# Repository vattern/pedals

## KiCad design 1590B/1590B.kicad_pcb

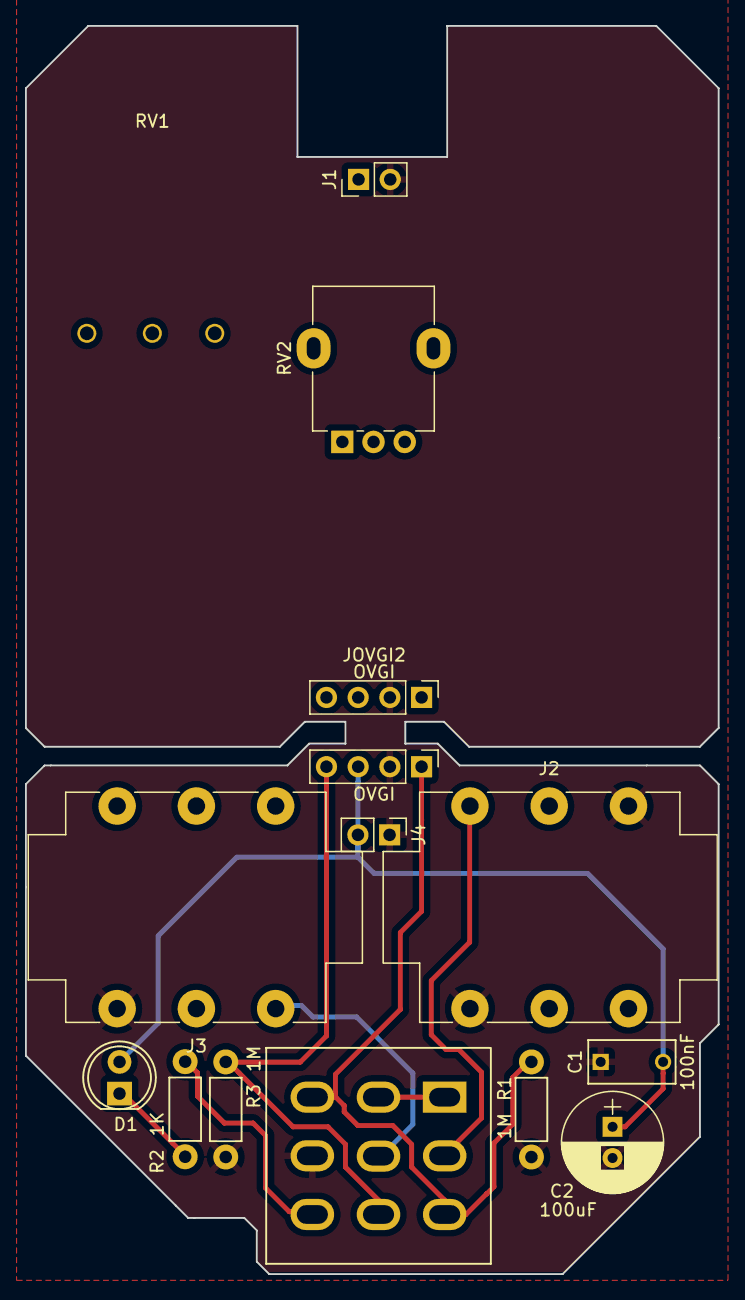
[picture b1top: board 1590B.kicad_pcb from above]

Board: 2 copper layers, 55.5 x 100.0 mm, 16 parts (0 on the bottom side), 9 nets.

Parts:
C1: 100nF; C_Rect_L7_W3.5_P5
C2: 100uF; CP_Radial_D8.0mm_P2.50mm
D1: LED; LED-5MM
J1, J4: V+ GND; PinHeader_1x02_P2.54mm_Vertical
J2, J3: NMJ6HCD2; Jack_6.35mm_Neutrik_NMJ6HCD2_Horizontal
JOVGI1, JOVGI2: OVGI; Pin_Header_Straight_1x04_Pitch2.54mm
N1: Housing; 1590B
R1, R3: 1M; Resistor_Horizontal_RM7mm
R2: 1K; Resistor_Horizontal_RM7mm
RV1: ALPHA-16mm; Potentiometer_ALPHA_RV16106N
RV2: ALPHA-9MM; Potentiometer_Alpha_RD901F-40-00D_Single_Vertical
SW1: SW_3PDT; 3PDT-Footswitch

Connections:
+9V: C1.2, C2.1, D1.2 (A), J1.1, J4.2, JOVGI1.3, JOVGI2.3
GND: C1.1, C2.2, J1.2, J2.S, J2.TN, J3.S, J4.1, JOVGI1.2, JOVGI2.2, R1.2, R3.2, SW1.6 (B)
I: JOVGI1.1, JOVGI2.1, R1.1, SW1.3 (A), SW1.7 (C)
unnamed: D1.1 (K), R2.1
unnamed: SW1.1 (A), SW1.2 (A)
unnamed: J2.T, SW1.4 (B)
unnamed: J3.T, SW1.5 (B)
unnamed: R2.2, SW1.9 (C)
O: JOVGI1.4, JOVGI2.4, R3.1, SW1.8 (C)

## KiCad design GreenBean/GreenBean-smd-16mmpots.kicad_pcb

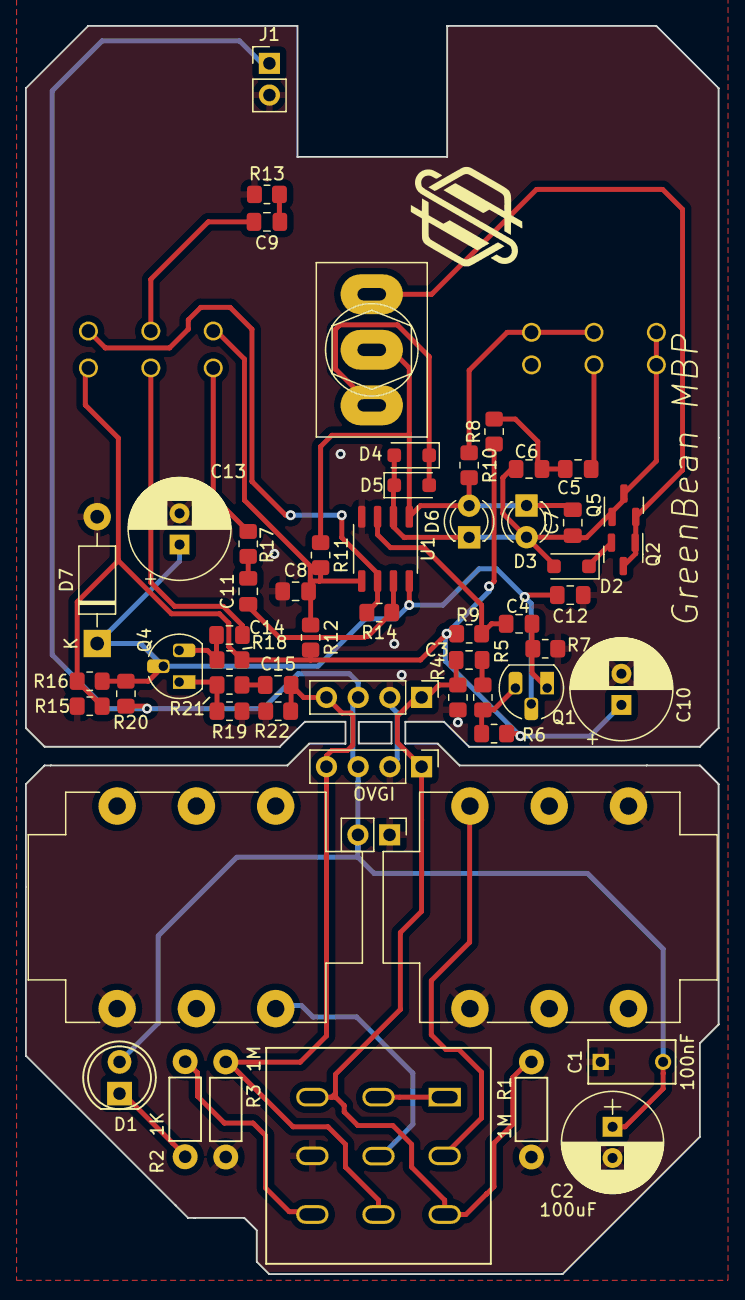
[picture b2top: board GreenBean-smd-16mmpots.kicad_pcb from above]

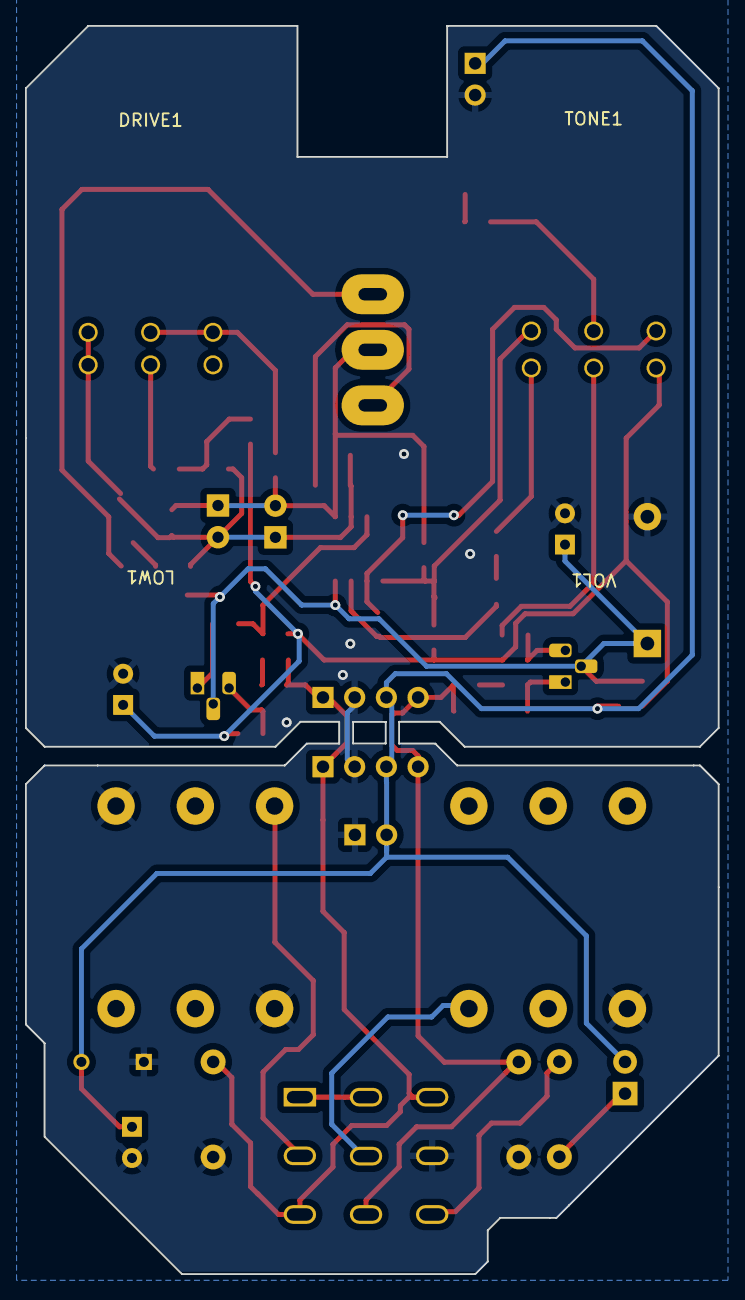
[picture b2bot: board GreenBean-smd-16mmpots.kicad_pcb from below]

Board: 2 copper layers, 55.5 x 100.0 mm, 62 parts (4 on the bottom side), 34 nets.

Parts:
C1: 100nF; C_Rect_L7_W3.5_P5
C2, C13: 100uF; CP_Radial_D8.0mm_P2.50mm
C3: 20n; C_0805_2012Metric_Pad1.18x1.45mm_HandSolder
C4, C11, C15: 1u; C_0805_2012Metric_Pad1.18x1.45mm_HandSolder
C5: 150n; C_0805_2012Metric_Pad1.18x1.45mm_HandSolder
C6: 47n; C_0805_2012Metric_Pad1.18x1.45mm_HandSolder
C7: 51p; C_0805_2012Metric_Pad1.18x1.45mm_HandSolder
C8, C9, C12: 220n; C_0805_2012Metric_Pad1.18x1.45mm_HandSolder
C10: 10uF; CP_Radial_D8.0mm_P2.50mm
C14: 100n; C_0805_2012Metric_Pad1.18x1.45mm_HandSolder
D1: LED; LED-5MM
D2: BAT41; D_SOD-123F
D3, D6: LED; LED_D3.0mm
D4, D5: 1N914; D_SOD-123F
D7: 1N4001; D_DO-41_SOD81_P10.16mm_Horizontal
DRIVE1: 500KA; Potentiometer_ALPHA_RV16106N
J1, J4: V+ GND; PinHeader_1x02_P2.54mm_Vertical
J2, J3: NMJ6HCD2; Jack_6.35mm_Neutrik_NMJ6HCD2_Horizontal
JOVGI1, JOVGI2: OVGI; Pin_Header_Straight_1x04_Pitch2.54mm
LOW1: 20KB; Potentiometer_ALPHA_RV16106N
N1: Housing; 1590B
Q1, Q4: 2SC1815; TO-92L_HandSolder
Q2, Q5: 2N7002; SOT-23
R1, R3: 1M; Resistor_Horizontal_RM7mm
R2: 1K; Resistor_Horizontal_RM7mm
R4: 1M; R_0805_2012Metric_Pad1.20x1.40mm_HandSolder
R5, R11, R14, R17: 1k; R_0805_2012Metric_Pad1.20x1.40mm_HandSolder
R6, R18: 510k; R_0805_2012Metric_Pad1.20x1.40mm_HandSolder
R7, R9, R12, R15, R16, R19, R22: 10k; R_0805_2012Metric_Pad1.20x1.40mm_HandSolder
R8: 4k7; R_0805_2012Metric_Pad1.20x1.40mm_HandSolder
R10: 51k; R_0805_2012Metric_Pad1.20x1.40mm_HandSolder
R13: 220R; R_0805_2012Metric_Pad1.20x1.40mm_HandSolder
R20: 47R; R_0805_2012Metric_Pad1.20x1.40mm_HandSolder
R21: 100R; R_0805_2012Metric_Pad1.20x1.40mm_HandSolder
SW1: SW_3PDT; 3PDT-Footswitch
SW2: SW_SPDT; SW_Toggle_Blue_wSlots
TONE1: 20KB; Potentiometer_ALPHA_RV16106N
U1: RC4558; SO-8_3.9x4.9mm_P1.27mm
VOL1: 100KB; Potentiometer_ALPHA_RV16106N

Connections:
+9V: C1.2, C2.1, D1.2 (A), J1.1, J4.2, JOVGI1.3, JOVGI2.3, R20.2
A: C6.2, C7.1, D2.2 (A), D3.2 (A), D4.2 (A), D5.1 (K), D6.1 (K), DRIVE1.1, LOW1.3, Q5.1 (G), Q5.3 (D), U1.2 (-)
B: C7.2, D3.1 (K), D6.2 (A), R10.2, R11.1, SW2.2, U1.1
GND: C1.1, C2.2, C8.1, C10.2, C12.1, C13.2, D7.2 (A), J1.2, J2.S, J2.TN, J3.S, J4.1, JOVGI1.2, JOVGI2.2, R1.2, R3.2, R4.1, R7.1, R13.1, R15.1, R19.1, R22.1, SW1.6 (B), U1.4 (V-)
I: C3.1, JOVGI1.1, JOVGI2.1, R1.1, R4.2, SW1.3 (A), SW1.7 (C)
unnamed: C3.2, R5.2
unnamed: C5.1, C6.1, R8.2
unnamed: C5.2, LOW1.2
unnamed: C9.1, R13.2
unnamed: C9.2, TONE1.2
unnamed: C11.1, R14.2, U1.7
unnamed: C11.2, R17.1
unnamed: C14.1, VOL1.2
unnamed: C15.1, R21.2
unnamed: D1.1 (K), R2.1
unnamed: D2.1 (K), Q2.2 (S)
unnamed: D4.1 (K), D5.2 (A), SW2.1
unnamed: DRIVE1.2, DRIVE1.3, R10.1
unnamed: Q1.3 (B), R5.1, R6.1
unnamed: C4.1, Q1.1 (E), R7.2
unnamed: Q2.1 (G), Q2.3 (D), Q5.2 (S), SW2.3
unnamed: C14.2, Q4.3 (B), R18.1
unnamed: Q4.1 (E), R19.2, R21.1
unnamed: R17.2, VOL1.3
unnamed: SW1.1 (A), SW1.2 (A)
unnamed: J2.T, SW1.4 (B)
unnamed: J3.T, SW1.5 (B)
unnamed: R2.2, SW1.9 (C)
unnamed: C4.2, R9.1, U1.3 (+)
unnamed: C8.2, R11.2, R12.1, TONE1.1, U1.5 (+)
unnamed: R14.1, TONE1.3, U1.6 (-)
O: C15.2, JOVGI1.4, JOVGI2.4, R3.1, R22.2, SW1.8 (C)
VB: C10.1, R6.2, R8.1, R9.2, R12.2, R15.2, R16.1, R18.2, VOL1.1
VC: C12.2, C13.1, D7.1 (K), Q1.2 (C), Q4.2 (C), R16.2, R20.1, U1.8 (V+)

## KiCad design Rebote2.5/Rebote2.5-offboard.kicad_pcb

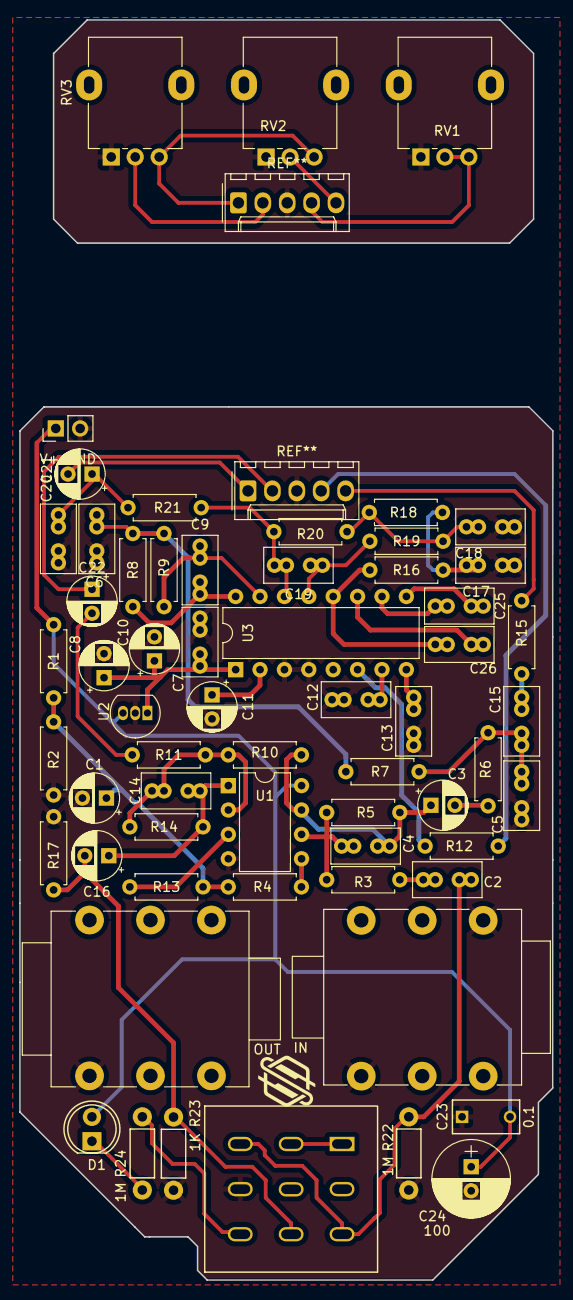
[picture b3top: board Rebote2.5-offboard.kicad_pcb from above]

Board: 2 copper layers, 55.5 x 91.0 mm, 62 parts (0 on the bottom side), 40 nets.

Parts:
C1, C8, C10, C11: 47uF; CP_Radial_D5.0mm_P2.50mm
C2: 8n2; C_Rect_L7.0mm_W3.5mm_P2.50mm_P5.00mm
C3, C16, C21, C22: 1uF; CP_Radial_D5.0mm_P2.50mm
C4: 5pF; C_Rect_L7.0mm_W3.5mm_P2.50mm_P5.00mm
C5: 27nF; C_Rect_L7.0mm_W3.5mm_P2.50mm_P5.00mm
C6, C17, C18: 10nF; C_Rect_L7.0mm_W3.5mm_P2.50mm_P5.00mm
C7, C12, C13, C15, C20: 100nF; C_Rect_L7.0mm_W3.5mm_P2.50mm_P5.00mm
C9: 560pF; C_Rect_L7.0mm_W3.5mm_P2.50mm_P5.00mm
C14: 51pF; C_Rect_L7.0mm_W3.5mm_P2.50mm_P5.00mm
C19: 1nF; C_Rect_L7.0mm_W3.5mm_P2.50mm_P5.00mm
C23: 0.1; C_Rect_L7_W3.5_P5
C24: 100; CP_Radial_D8.0mm_P2.50mm
C25, C26: 82nF; C_Rect_L7.0mm_W3.5mm_P2.50mm_P5.00mm
D1: LED; LED-5MM
J1: V+ GND; Pin_Header_Straight_1x02_Pitch2.54mm
J2: IN; NMJ6HCD2
J3: OUT; NMJ6HCD2
N1: Housing; 1590B
R1, R2, R6, R7, R8, R16, R18, R19: 12K; R_Axial_DIN0207_L6.3mm_D2.5mm_P7.62mm_Horizontal
R3, R4, R5: 510K; R_Axial_DIN0207_L6.3mm_D2.5mm_P7.62mm_Horizontal
R9: 47K; R_Axial_DIN0207_L6.3mm_D2.5mm_P7.62mm_Horizontal
R10, R14, R20: 24K; R_Axial_DIN0207_L6.3mm_D2.5mm_P7.62mm_Horizontal
R11: 33K; R_Axial_DIN0207_L6.3mm_D2.5mm_P7.62mm_Horizontal
R12, R13: 1k; R_Axial_DIN0207_L6.3mm_D2.5mm_P7.62mm_Horizontal
R15: 15K; R_Axial_DIN0207_L6.3mm_D2.5mm_P7.62mm_Horizontal
R17: 100K; R_Axial_DIN0207_L6.3mm_D2.5mm_P7.62mm_Horizontal
R21: 2k7; R_Axial_DIN0207_L6.3mm_D2.5mm_P7.62mm_Horizontal
R22, R24: 1M; Resistor_Horizontal_RM7mm
R23: 1K; Resistor_Horizontal_RM7mm
RV1: 50KB; Potentiometer_Alpha_RD901F-40-00D_Single_Vertical
RV2: 25KB; Potentiometer_Alpha_RD901F-40-00D_Single_Vertical
RV3: 100KB; Potentiometer_Alpha_RD901F-40-00D_Single_Vertical
SW1: SW_3PDT; 3PDT-Footswitch
U1: TL072; DIP-8_W7.62mm
U2: L78L05_TO92; TO-92_Inline
U3: PT2399; DIP-16_W7.62mm

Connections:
+5V: C7.2, C8.1, C10.1, U2.1 (VO), U3.1 (VCC)
+9V: C23.2, C24.1, D1.2 (A), J1.1, R1.1, U1.8 (V+), U2.3 (VI)
AI: C3.1, C4.2, R5.2, R10.1, U1.7
DELAY_OUT: C26.2, R16.1, U3.12 (OP2-OUT)
GND: C1.2, C5.1, C6.1, C7.1, C8.2, C10.2, C11.2, C12.1, C13.1, C17.1, C18.1, C20.1, C23.1, C24.2, J1.2, J2.1 (S), J2.5 (TN), J3.1 (S), R2.2, R17.1, R22.2, R23.2, RV1.1, RV2.1, RV3.1, SW1.6 (B), U1.4 (V-), U2.2 (GND), U3.3 (AGND), U3.4 (DGND)
I: C2.1, R22.1, SW1.3 (A), SW1.7 (C)
LPF1-IN: C9.1, R8.2, U3.16 (LPF1-IN)
LPF1-OUT: C9.2, R9.2, U3.15 (LPF1-OUT)
LPF2-IN: C19.1, R19.2, U3.13 (LPF2-IN)
LPF2-OUT: C19.2, R20.2, R21.1, U3.14 (LPF2-OUT)
unnamed: C2.2, R3.1
unnamed: C3.2, R6.1
unnamed: C6.2, R7.2, R8.1, R9.1
unnamed: C14.2, C16.1, R14.2, U1.1
unnamed: C5.2, C15.1, R6.2, R7.1
unnamed: C15.2, R15.1
unnamed: C17.2, R16.2, R18.1
unnamed: C18.2, R18.2, R19.1, R20.1
unnamed: C20.2, C21.1, R21.2
unnamed: C21.2, RV2.3, RV3.3
unnamed: C22.1, RV3.2
unnamed: C22.2, R11.1
unnamed: D1.1 (K), R24.1
unnamed: R12.2, RV1.2, RV1.3
unnamed: R15.2, RV2.2
unnamed: SW1.1 (A), SW1.2 (A)
unnamed: R24.2, SW1.9 (C)
unnamed: R13.2, U1.3 (+)
unnamed: C14.1, R10.2, R11.2, R14.1, U1.2 (-)
unnamed: R4.2, U1.5 (+)
unnamed: C4.1, R3.2, R5.1, U1.6 (-)
unnamed: C13.2, U3.8 (CC0)
unnamed: C12.2, U3.7 (CC1)
unnamed: C25.2, U3.10 (OP1-IN)
unnamed: C25.1, U3.9 (OP1-OUT)
unnamed: C26.1, U3.11 (OP2-IN)
unnamed: C11.1, U3.2 (REF)
unnamed: R12.1, U3.6 (VCO)
O: C16.2, R17.2, R23.1, SW1.8 (C)
VD: C1.1, R1.2, R2.1, R4.1, R13.1

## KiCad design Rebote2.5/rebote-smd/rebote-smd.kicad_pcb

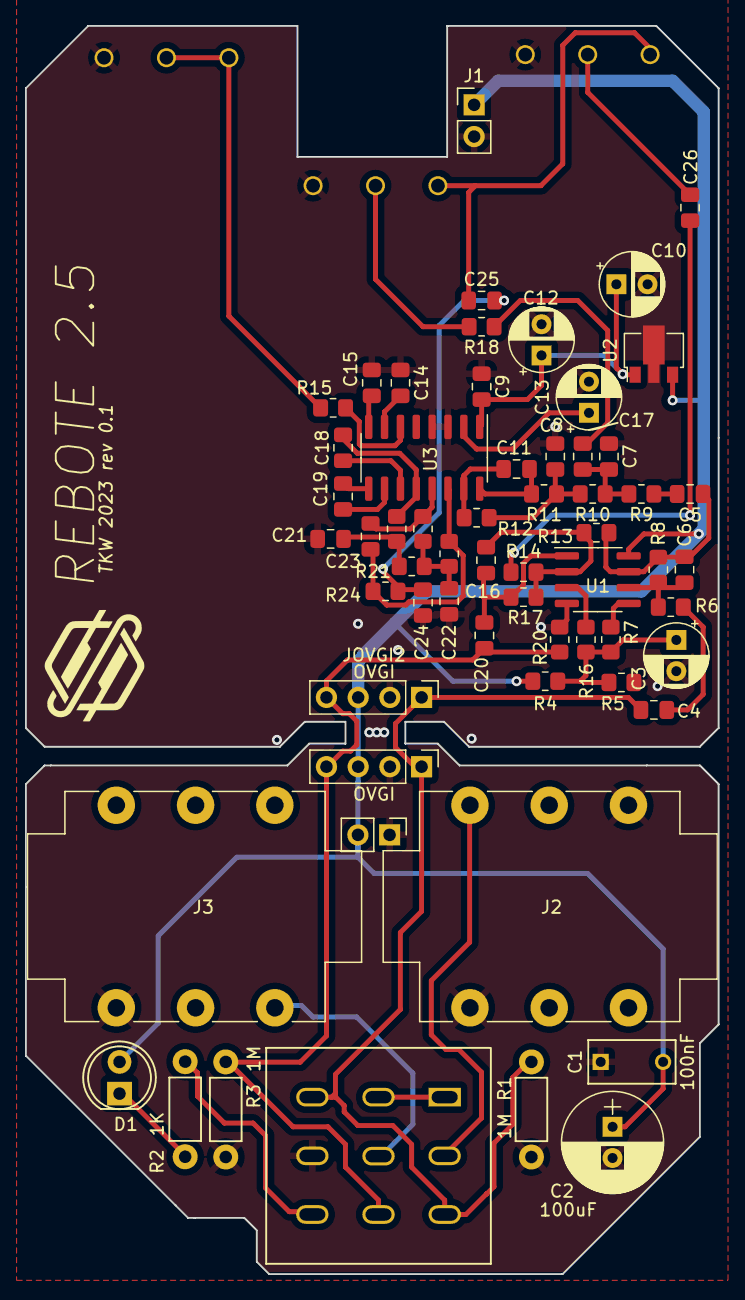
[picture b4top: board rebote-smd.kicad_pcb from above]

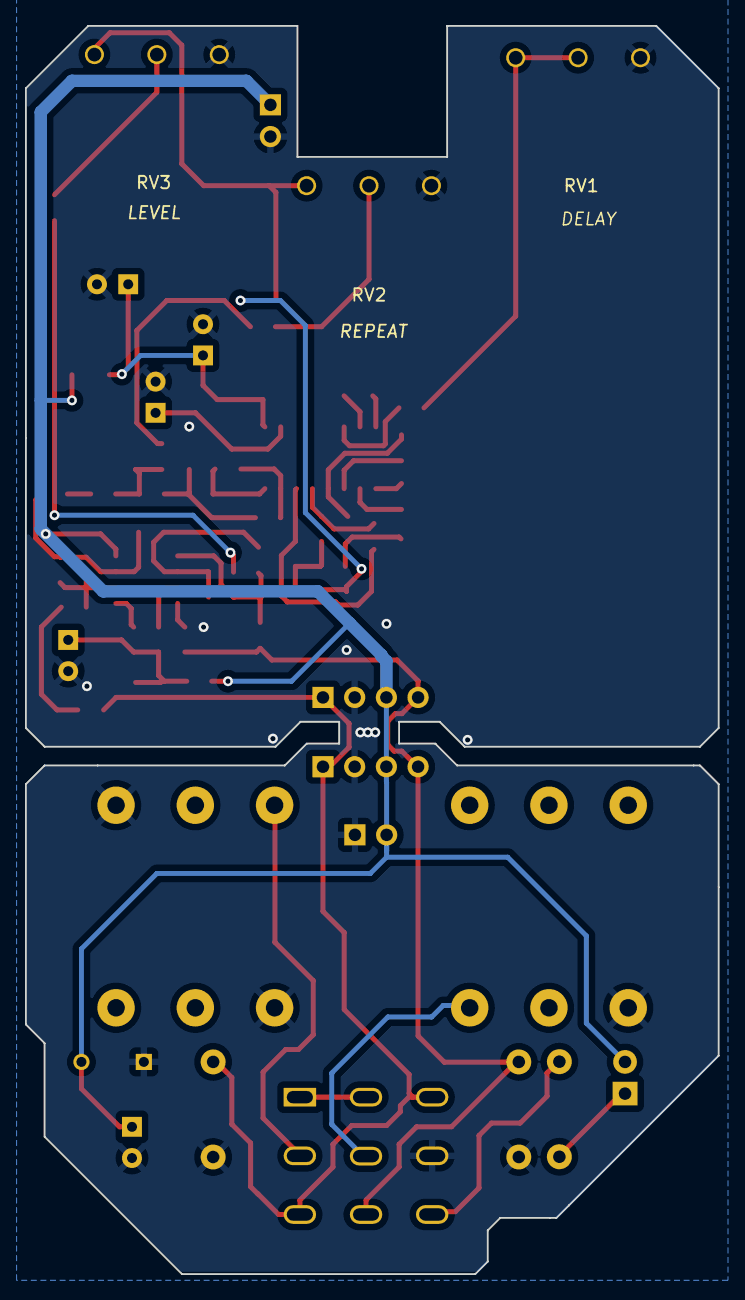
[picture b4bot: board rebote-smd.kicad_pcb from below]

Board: 2 copper layers, 55.5 x 100.0 mm, 65 parts (3 on the bottom side), 42 nets.

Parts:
C1: 100nF; C_Rect_L7_W3.5_P5
C2: 100uF; CP_Radial_D8.0mm_P2.50mm
C3, C10, C12, C13: 47uF; CP_Radial_D5.0mm_P2.50mm
C4: 8n2; C_0805_2012Metric_Pad1.18x1.45mm_HandSolder
C5, C20, C25, C26: 1uF; C_0805_2012Metric_Pad1.18x1.45mm_HandSolder
C6: 5pF; C_0805_2012Metric_Pad1.18x1.45mm_HandSolder
C7: 27nF; C_0805_2012Metric_Pad1.18x1.45mm_HandSolder
C8, C21, C22: 10nF; C_0805_2012Metric_Pad1.18x1.45mm_HandSolder
C9, C14, C15, C17, C24: 100nF; C_0805_2012Metric_Pad1.18x1.45mm_HandSolder
C11: 560pF; C_0805_2012Metric_Pad1.18x1.45mm_HandSolder
C16: 51pF; C_0805_2012Metric_Pad1.18x1.45mm_HandSolder
C18, C19: 82nF; C_0805_2012Metric_Pad1.18x1.45mm_HandSolder
C23: 1nF; C_0805_2012Metric_Pad1.18x1.45mm_HandSolder
D1: LED; LED-5MM
J1, J4: V+ GND; PinHeader_1x02_P2.54mm_Vertical
J2, J3: NMJ6HCD2; Jack_6.35mm_Neutrik_NMJ6HCD2_Horizontal
JOVGI1, JOVGI2: OVGI; Pin_Header_Straight_1x04_Pitch2.54mm
N1: Housing; 1590B
R1, R3: 1M; Resistor_Horizontal_RM7mm
R2: 1K; Resistor_Horizontal_RM7mm
R4, R5, R9, R10, R11, R19, R21, R22: 12K; R_0805_2012Metric_Pad1.20x1.40mm_HandSolder
R6, R7, R8: 510K; R_0805_2012Metric_Pad1.20x1.40mm_HandSolder
R12: 47K; R_0805_2012Metric_Pad1.20x1.40mm_HandSolder
R13, R17, R23: 24K; R_0805_2012Metric_Pad1.20x1.40mm_HandSolder
R14: 33K; R_0805_2012Metric_Pad1.20x1.40mm_HandSolder
R15, R16: 1k; R_0805_2012Metric_Pad1.20x1.40mm_HandSolder
R18: 15K; R_0805_2012Metric_Pad1.20x1.40mm_HandSolder
R20: 100K; R_0805_2012Metric_Pad1.20x1.40mm_HandSolder
R24: 2k7; R_0805_2012Metric_Pad1.20x1.40mm_HandSolder
RV1: 50KB; Potentiometer_ALPHA_RV16106N
RV2: 25KB; Potentiometer_ALPHA_RV16106N
RV3: 100KB; Potentiometer_ALPHA_RV16106N
SW1: SW_3PDT; 3PDT-Footswitch
U1: TL072; SOIC-8_3.9x4.9mm_P1.27mm
U2: L78L05_SOT89; SOT-89-3
U3: PT2399; SOIC-16_3.9x9.9mm_P1.27mm

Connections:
+5V: C9.2, C10.1, C12.1, U2.1 (OUT), U3.1 (VCC)
+9V: C1.2, C2.1, D1.2 (A), J1.1, J4.2, JOVGI1.3, JOVGI2.3, R4.1, U1.8 (V+), U2.3 (IN)
AI: C5.1, C6.2, R8.2, R13.1, U1.7
DELAY_OUT: C18.2, R19.1, U3.12 (OP2-OUT)
GND: C1.1, C2.2, C3.2, C7.1, C8.1, C9.1, C10.2, C12.2, C13.2, C14.1, C15.1, C21.1, C22.1, C24.1, J1.2, J2.S, J2.TN, J3.S, J4.1, JOVGI1.2, JOVGI2.2, R1.2, R3.2, R5.2, R20.1, RV1.1, RV2.1, RV3.1, SW1.6 (B), U1.4 (V-), U2.2 (GND), U3.3 (AGND), U3.4 (DGND)
I: C4.1, JOVGI1.1, JOVGI2.1, R1.1, SW1.3 (A), SW1.7 (C)
LPF1-IN: C11.1, R11.2, U3.16 (LPF1-IN)
LPF1-OUT: C11.2, R12.2, U3.15 (LPF1-OUT)
LPF2-IN: C23.1, R22.2, U3.13 (LPF2-IN)
LPF2-OUT: C23.2, R23.2, R24.1, U3.14 (LPF2-OUT)
unnamed: C4.2, R6.1
unnamed: C5.2, R9.1
unnamed: C8.2, R10.2, R11.1, R12.1
unnamed: C16.2, C20.1, R17.2, U1.1
unnamed: C7.2, C17.1, R9.2, R10.1
unnamed: C17.2, R18.1
unnamed: C21.2, R19.2, R21.1
unnamed: C22.2, R21.2, R22.1, R23.1
unnamed: C24.2, C25.1, R24.2
unnamed: C25.2, RV2.3, RV3.3
unnamed: C26.1, RV3.2
unnamed: C26.2, R14.1
unnamed: D1.1 (K), R2.1
unnamed: R15.2, RV1.2, RV1.3
unnamed: R18.2, RV2.2
unnamed: SW1.1 (A), SW1.2 (A)
unnamed: J2.T, SW1.4 (B)
unnamed: J3.T, SW1.5 (B)
unnamed: R2.2, SW1.9 (C)
unnamed: R16.2, U1.3 (+)
unnamed: C16.1, R13.2, R14.2, R17.1, U1.2 (-)
unnamed: R7.2, U1.5 (+)
unnamed: C6.1, R6.2, R8.1, U1.6 (-)
unnamed: C15.2, U3.8 (CC0)
unnamed: C14.2, U3.7 (CC1)
unnamed: C19.2, U3.10 (OP1-IN)
unnamed: C19.1, U3.9 (OP1-OUT)
unnamed: C18.1, U3.11 (OP2-IN)
unnamed: C13.1, U3.2 (REF)
unnamed: R15.1, U3.6 (VCO)
O: C20.2, JOVGI1.4, JOVGI2.4, R3.1, R20.2, SW1.8 (C)
VD: C3.1, R4.2, R5.1, R7.1, R16.1

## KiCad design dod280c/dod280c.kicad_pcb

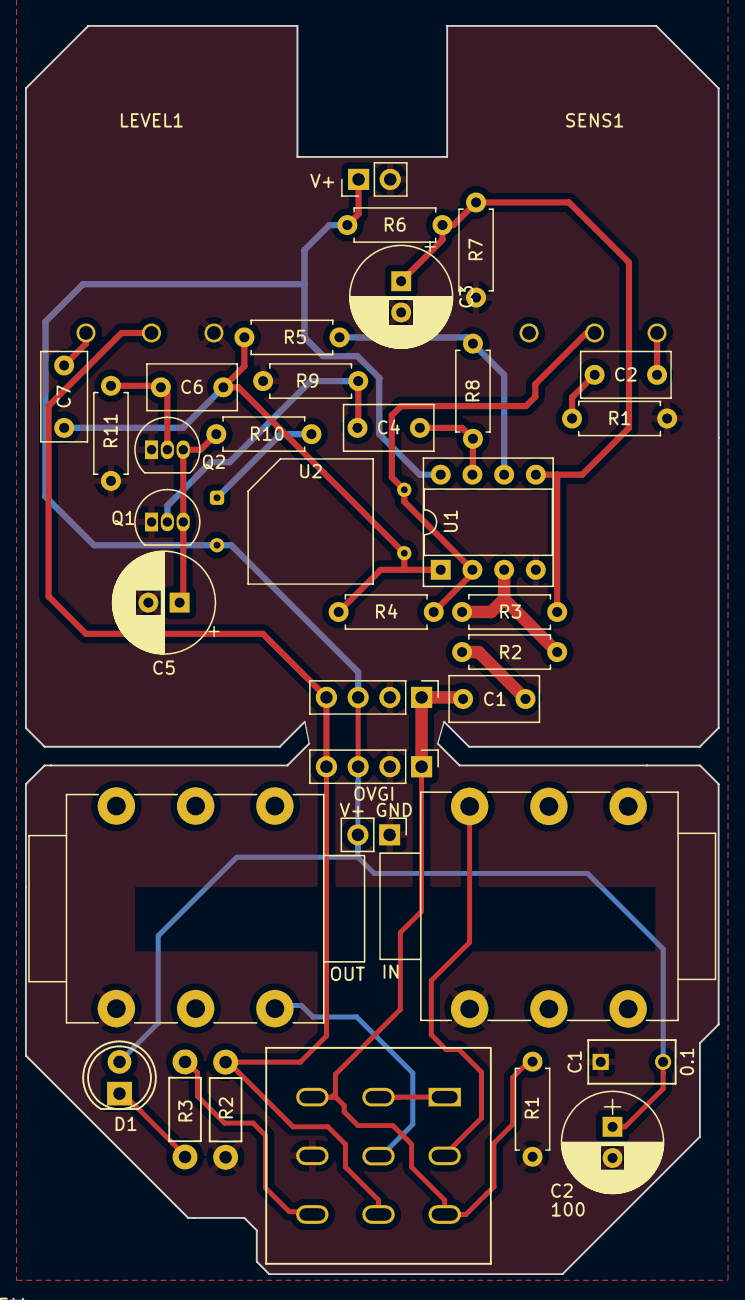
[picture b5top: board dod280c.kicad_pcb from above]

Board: 2 copper layers, 55.5 x 100.0 mm, 37 parts (0 on the bottom side), 23 nets.

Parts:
C1: 10nF; C_Rect_L7.0mm_W3.5mm_P5.00mm
C1#2: 0.1; C_Rect_L7_W3.5_P5
C2, C4, C6, C7: 50nF; C_Rect_L7.0mm_W3.5mm_P5.00mm
C2#2: 100; CP_Radial_D8.0mm_P2.50mm
C3: 10uF; CP_Radial_D8.0mm_P2.50mm
C5: 47uF; CP_Radial_D8.0mm_P2.50mm
D1: LED; LED-5MM
J1: V+; Pin_Header_Straight_1x02_Pitch2.54mm
J2: IN; NMJ6HCD2
J3: OUT; NMJ6HCD2
J4: V+ GND; Pin_Header_Straight_1x02_Pitch2.54mm
JOVGI1, JOVGI2: OVGI; Pin_Header_Straight_1x04_Pitch2.54mm
LEVEL1: 100KA; Potentiometer_ALPHA_RV16106N
Q1, Q2: 2N3904; TO-92_Inline
R1: R; R_Axial_DIN0207_L6.3mm_D2.5mm_P7.62mm_Horizontal
R1#2, R6, R7: 22K; R_Axial_DIN0207_L6.3mm_D2.5mm_P7.62mm_Horizontal
R2: 1M; Resistor_Horizontal_RM7mm
R2#2: 10K; R_Axial_DIN0207_L6.3mm_D2.5mm_P7.62mm_Horizontal
R3: 1K; Resistor_Horizontal_RM7mm
R3#2: 470K; R_Axial_DIN0207_L6.3mm_D2.5mm_P7.62mm_Horizontal
R4: 1M; R_Axial_DIN0207_L6.3mm_D2.5mm_P7.62mm_Horizontal
R5, R8: 100K; R_Axial_DIN0207_L6.3mm_D2.5mm_P7.62mm_Horizontal
R9, R11: 220K; R_Axial_DIN0207_L6.3mm_D2.5mm_P7.62mm_Horizontal
R10: 4K7; R_Axial_DIN0207_L6.3mm_D2.5mm_P7.62mm_Horizontal
SENS1: 500KB; Potentiometer_ALPHA_RV16106N
SW1: SW_3PDT; 3PDT-Footswitch
U1: LM358; DIP-8_W7.62mm_Socket
U2: VTL5C; PerkinElmer_VTL5C

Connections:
+9V: C1#2.2, C2#2.1, D1.2, J1.1, J4.2, JOVGI1.3, JOVGI2.3, R6.1, U1.8 (V+), U2.2 (+)
GND: C1#2.1, C2#2.2, C3.2, C5.2, J1.2, J2.1, J2.5, J3.1, J4.1, JOVGI1.2, JOVGI2.2, LEVEL1.3, Q1.1 (E), Q2.1 (E), R1.1, R1#2.2, R2.2, R7.2, R9.2, R11.2, SW1.6, U1.4 (V-)
unnamed: C1.2, R2#2.1
unnamed: C2.1, R1#2.1
unnamed: C2.2, SENS1.3
unnamed: C4.1, R8.2, U1.7
unnamed: C6.2, C7.1, R4.2, R5.1, U1.1, U2.4
unnamed: C7.2, LEVEL1.1
unnamed: D1.1, R3.1
unnamed: J2.2, SW1.4
unnamed: J3.2, SW1.5
unnamed: C4.2, Q1.2 (B), R9.1
unnamed: C5.1, Q1.3 (C), Q2.3 (C), R10.2
unnamed: C6.1, Q2.2 (B), R11.1
unnamed: R3.2, SW1.9
unnamed: SW1.1, SW1.2
unnamed: R2#2.2, R3#2.2, U1.3 (+)
unnamed: R4.1, SENS1.2, U1.2 (-), U2.3
unnamed: R5.2, R8.1, U1.6 (-)
unnamed: R10.1, U2.1 (-)
VB: C3.1, R3#2.1, R6.2, R7.1, U1.5 (+)
/I: C1.1, JOVGI1.1, JOVGI2.1, R1.2, SW1.3, SW1.7
/O: JOVGI1.4, JOVGI2.4, LEVEL1.2, R2.1, SW1.8

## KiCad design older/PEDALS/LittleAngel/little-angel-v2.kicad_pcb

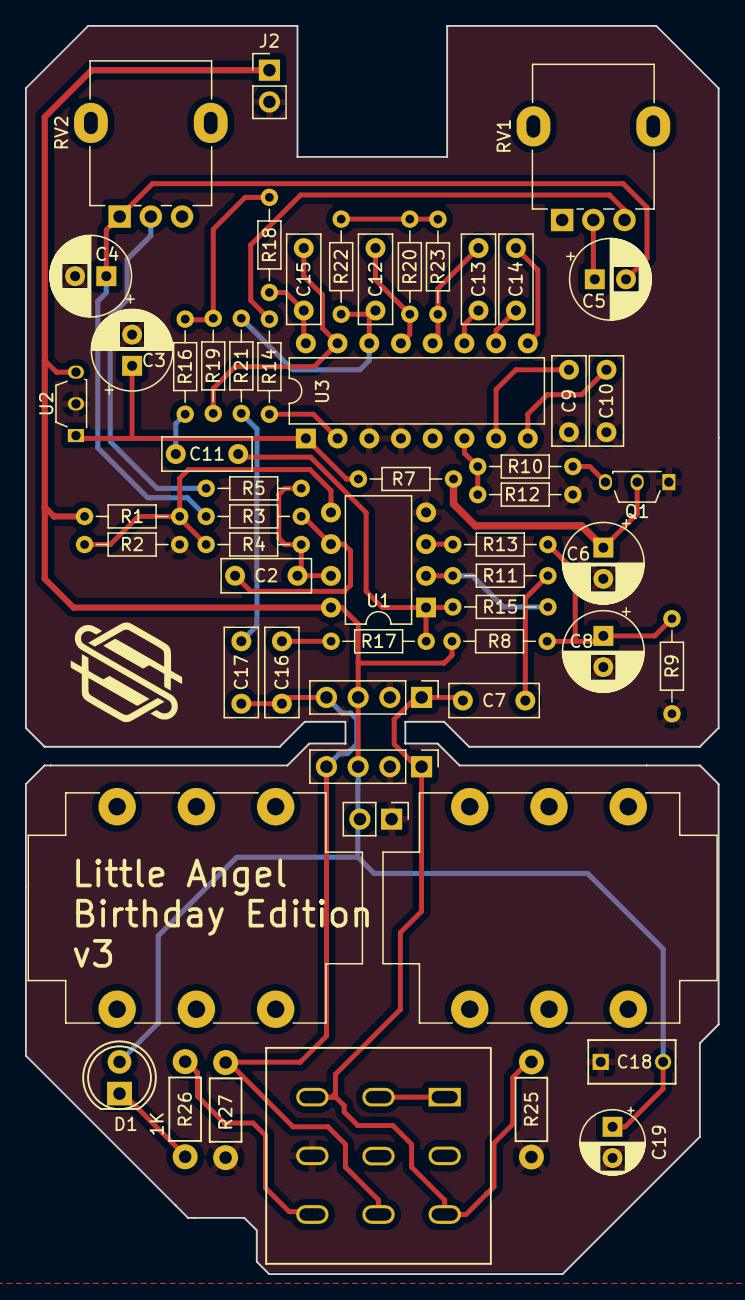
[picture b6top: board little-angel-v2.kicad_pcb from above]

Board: 2 copper layers, 55.5 x 100.0 mm, 58 parts (0 on the bottom side), 39 nets.

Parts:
C2: 10nF; C_Disc_D7.0mm_W2.5mm_P5.00mm
C3, C6, C8: 47uF; CP_Radial_D6.3mm_P2.50mm
C4, C5: 10uF; CP_Radial_D6.3mm_P2.50mm
C7, C9, C10, C11, C16, C17: 100nF; C_Disc_D7.0mm_W2.5mm_P5.00mm
C12: 10n; C_Disc_D7.0mm_W2.5mm_P5.00mm
C13, C14: 100n; C_Disc_D7.0mm_W2.5mm_P5.00mm
C15: 3n3; C_Disc_D7.0mm_W2.5mm_P5.00mm
C18: 100nF; C_Rect_L7_W3.5_P5
C19: 100uF; CP_Radial_D5.0mm_P2.50mm
D1: LED; LED-5MM
J1: IN; Jack_6.35mm_Neutrik_NMJ6HCD2_Horizontal
J2, J3: V+ GND; PinHeader_1x02_P2.54mm_Vertical
J4: OUT; Jack_6.35mm_Neutrik_NMJ6HCD2_Horizontal
JOVGI1, JOVGI2: OVGI; Pin_Header_Straight_1x04_Pitch2.54mm
N1: Housing; 1590B
Q1: 2N3904; TO-92S_Wide
R1: 100k; R_Axial_DIN0204_L3.6mm_D1.6mm_P7.62mm_Horizontal
R2: 47k; R_Axial_DIN0204_L3.6mm_D1.6mm_P7.62mm_Horizontal
R3: 220K; R_Axial_DIN0204_L3.6mm_D1.6mm_P7.62mm_Horizontal
R4: 220k; R_Axial_DIN0204_L3.6mm_D1.6mm_P7.62mm_Horizontal
R5: 4k7; R_Axial_DIN0204_L3.6mm_D1.6mm_P7.62mm_Horizontal
R7: 68K; R_Axial_DIN0204_L3.6mm_D1.6mm_P7.62mm_Horizontal
R8, R9, R16, R17, R18, R19, R20, R21, R22, R23: 10k; R_Axial_DIN0204_L3.6mm_D1.6mm_P7.62mm_Horizontal
R10: 100R; R_Axial_DIN0204_L3.6mm_D1.6mm_P7.62mm_Horizontal
R11: 470k; R_Axial_DIN0204_L3.6mm_D1.6mm_P7.62mm_Horizontal
R12: 2k2; R_Axial_DIN0204_L3.6mm_D1.6mm_P7.62mm_Horizontal
R13: 330k; R_Axial_DIN0204_L3.6mm_D1.6mm_P7.62mm_Horizontal
R14: 33k; R_Axial_DIN0204_L3.6mm_D1.6mm_P7.62mm_Horizontal
R15: 1M; R_Axial_DIN0204_L3.6mm_D1.6mm_P7.62mm_Horizontal
R25: 1M; Resistor_Horizontal_RM7mm
R26: 1K; Resistor_Horizontal_RM7mm
R27: 100K; Resistor_Horizontal_RM7mm
RV1: 470K lin; Potentiometer_Alpha_RD901F-40-00D_Single_Vertical
RV2: 100k lin; Potentiometer_Alpha_RD901F-40-00D_Single_Vertical
SW1: SW_3PDT; 3PDT-Footswitch
U1: NE5532; DIP-8_W7.62mm
U2: L78L05_TO92; TO-92S_Wide
U3: PT2399; DIP-16_W7.62mm

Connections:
+5V: C3.1, R7.2, U2.1 (VO), U3.1 (VCC)
+9V: C18.2, C19.1, D1.2 (A), J2.1, J3.2, JOVGI1.3, JOVGI2.3, R1.2, R8.2, U1.8 (V+), U2.3 (VI)
GND: C3.2, C4.2, C6.2, C8.2, C9.1, C10.1, C18.1, C19.2, J2.2, J3.1, JOVGI1.2, JOVGI2.2, Q1.1 (E), R2.1, R9.1, R12.1, R25.2, R27.2, SW1.6 (B), U1.4 (V-), U2.2 (GND), U3.3 (AGND), U3.4 (DGND)
I: C7.1, JOVGI1.1, JOVGI2.1, R25.1, SW1.3 (A), SW1.7 (C)
unnamed: C2.2, R4.2, R5.1, U1.7
unnamed: C4.1, C5.2, R3.2, RV2.1
unnamed: C5.1, RV1.2
unnamed: C7.2, R11.1
unnamed: C8.1, R8.1, R9.2, R13.1
unnamed: C11.1, R16.1
unnamed: C11.2, R15.2, R17.1, U1.1
unnamed: C16.1, R17.2
unnamed: C17.1, R21.2
unnamed: D1.1 (K), R26.1
unnamed: C6.1, Q1.2 (B), R7.1
unnamed: Q1.3 (C), R10.1
unnamed: R5.2, RV2.2
unnamed: R14.1, RV1.3
unnamed: R16.2, R18.2, R19.2
unnamed: R20.1, R22.1, R23.1
unnamed: SW1.1 (A), SW1.2 (A)
unnamed: R26.2, SW1.9 (C)
unnamed: R13.2, U1.3 (+)
unnamed: R11.2, R15.1, U1.2 (-)
unnamed: R1.1, R2.2, R4.1, U1.5 (+)
unnamed: C2.1, R3.1, U1.6 (-)
unnamed: C10.2, U3.8 (CC0)
unnamed: C9.2, U3.7 (CC1)
unnamed: C15.1, R18.1, U3.16 (LPF1-IN)
unnamed: C15.2, R19.1, U3.15 (LPF1-OUT)
unnamed: C12.2, R20.2, U3.13 (LPF2-IN)
unnamed: C12.1, R21.1, R22.2, U3.14 (LPF2-OUT)
unnamed: C14.1, U3.10 (OP1-IN)
unnamed: C14.2, U3.9 (OP1-OUT)
unnamed: C13.2, U3.11 (OP2-IN)
unnamed: C13.1, R23.2, U3.12 (OP2-OUT)
unnamed: R14.2, U3.2 (REF)
unnamed: R10.2, R12.2, U3.6 (VCO)
O: C16.2, C17.2, JOVGI1.4, JOVGI2.4, R27.1, SW1.8 (C)

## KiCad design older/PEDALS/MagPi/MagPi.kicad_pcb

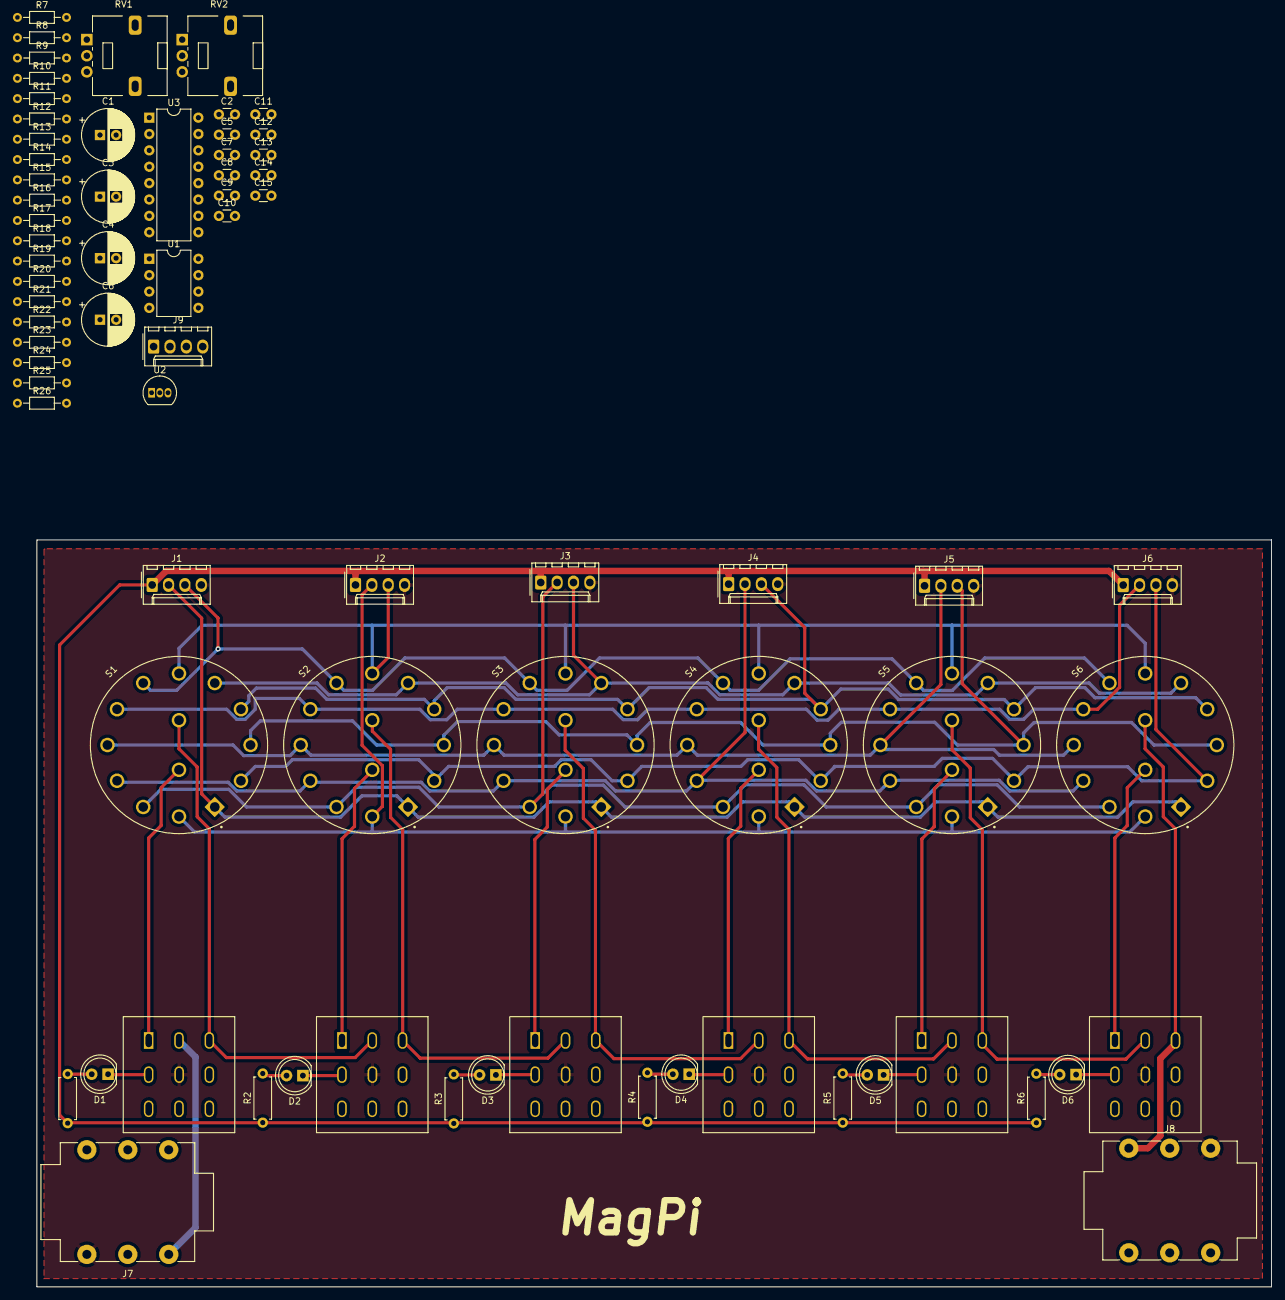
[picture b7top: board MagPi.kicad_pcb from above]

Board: 2 copper layers, 191.5 x 115.9 mm, 73 parts (0 on the bottom side), 68 nets.

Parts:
C1: 100uF; CP_Radial_D8.0mm_P2.50mm
C2, C11, C12: 10nF; C_Disc_D3.0mm_W1.6mm_P2.50mm
C3: 47uF; CP_Radial_D8.0mm_P2.50mm
C4, C6: 10uF; CP_Radial_D8.0mm_P2.50mm
C5, C7, C8, C9, C14, C15: 100nF; C_Disc_D3.0mm_W1.6mm_P2.50mm
C10, C13: 1nF; C_Disc_D3.0mm_W1.6mm_P2.50mm
D1, D2, D3, D4, D5, D6: LED; LED_D5.0mm
J1, J2, J3, J4, J5, J6, J9: Conn_01x04; Molex_KK-254_AE-6410-04A_1x04_P2.54mm_Vertical
J7, J8: NMJ6HCD2; Jack_6.35mm_Neutrik_NMJ6HCD2_Horizontal
R1, R2, R3, R4, R5, R6: R_Small; R_Axial_DIN0207_L6.3mm_D2.5mm_P7.62mm_Horizontal
R7, R26: 100k; R_Axial_DIN0204_L3.6mm_D1.6mm_P7.62mm_Horizontal
R8: 47k; R_Axial_DIN0204_L3.6mm_D1.6mm_P7.62mm_Horizontal
R9: 220K; R_Axial_DIN0204_L3.6mm_D1.6mm_P7.62mm_Horizontal
R10: 220k; R_Axial_DIN0204_L3.6mm_D1.6mm_P7.62mm_Horizontal
R11, R17: 1M; R_Axial_DIN0204_L3.6mm_D1.6mm_P7.62mm_Horizontal
R12: 4k7; R_Axial_DIN0204_L3.6mm_D1.6mm_P7.62mm_Horizontal
R13: 470k; R_Axial_DIN0204_L3.6mm_D1.6mm_P7.62mm_Horizontal
R14: 330k; R_Axial_DIN0204_L3.6mm_D1.6mm_P7.62mm_Horizontal
R15: 33k; R_Axial_DIN0204_L3.6mm_D1.6mm_P7.62mm_Horizontal
R16: 100R; R_Axial_DIN0204_L3.6mm_D1.6mm_P7.62mm_Horizontal
R18, R19, R20, R21, R22, R23, R24, R25: 10k; R_Axial_DIN0204_L3.6mm_D1.6mm_P7.62mm_Horizontal
RV1: 470K lin; Potentiometer_Alps_RK09L_Single_Vertical
RV2: 100k lin; Potentiometer_Alps_RK09L_Single_Vertical
S1, S2, S3, S4, S5, S6: CK1050; SW_CK1050
SW1, SW2, SW3, SW4, SW5, SW6: switches:SW_3PDT; 3PDT-Footswitch
U1: NE5532; DIP-8_W7.62mm
U2: L78L05_TO92; TO-92_Inline
U3: PT2399; DIP-16_W7.62mm

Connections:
+9V: C1.1, J1.1, J2.1, J3.1, J4.1, J5.1, J6.1, J9.1, R1.1, R2.1, R3.1, R4.1, R5.1, R6.1, R7.2, U1.8 (V+), U2.3 (VI)
GND: C1.2, C3.2, C4.2, C7.1, C8.1, J1.4, J2.4, J3.4, J4.4, J5.4, J6.4, J7.S, J8.S, J9.4, R8.1, R11.2, R16.1, R26.1, SW1.5 (B), SW2.5 (B), SW3.5 (B), SW4.5 (B), SW5.5 (B), SW6.5 (B), U1.4 (V-), U2.2 (GND), U3.3 (AGND), U3.4 (DGND)
I1: C5.1, J1.2, J9.2, R11.1, S1.1, S2.1, S3.1, S4.1, S5.1, S6.1
I2: J2.2, S1.2, S2.2, S3.2, S4.2, S5.2, S6.2
I3: J3.2, S1.3, S2.3, S3.3, S4.3, S5.3, S6.3
I4: J4.2, S1.4, S2.4, S3.4, S4.4, S5.4, S6.4
I5: J5.2, S1.5, S2.5, S3.5, S4.5, S5.5, S6.5
I6: J6.2, S1.6, S2.6, S3.6, S4.6, S5.6, S6.6
IP: J7.T, SW1.4 (B)
unnamed: C2.2, R10.2, R12.1, U1.7
unnamed: C4.1, C6.2, R9.2, RV2.3
unnamed: C5.2, R13.1
unnamed: C6.1, RV1.2
unnamed: C9.1, R18.1
unnamed: C9.2, R17.2, R19.1, U1.1
unnamed: C14.1, R19.2
unnamed: C15.1, R23.2
unnamed: D1.2 (A), R1.2
unnamed: D1.1 (K), SW1.2 (A)
unnamed: D2.2 (A), R2.2
unnamed: D2.1 (K), SW2.2 (A)
unnamed: D3.2 (A), R3.2
unnamed: D3.1 (K), SW3.2 (A)
unnamed: D4.2 (A), R4.2
unnamed: D4.1 (K), SW4.2 (A)
unnamed: D5.2 (A), R5.2
unnamed: D5.1 (K), SW5.2 (A)
unnamed: D6.2 (A), R6.2
unnamed: D6.1 (K), SW6.2 (A)
unnamed: R12.2, RV2.2
unnamed: R15.1, RV1.1
unnamed: R18.2, R20.2, R21.2
unnamed: R22.1, R24.1, R25.1
unnamed: S1.A, SW1.1 (A)
unnamed: S1.C, SW1.7 (C), SW2.4 (B)
unnamed: S2.A, SW2.1 (A)
unnamed: S2.C, SW2.7 (C), SW3.4 (B)
unnamed: S3.A, SW3.1 (A)
unnamed: S3.C, SW3.7 (C), SW4.4 (B)
unnamed: S4.A, SW4.1 (A)
unnamed: S4.C, SW4.7 (C), SW5.4 (B)
unnamed: S5.A, SW5.1 (A)
unnamed: S5.C, SW5.7 (C), SW6.4 (B)
unnamed: S6.A, SW6.1 (A)
unnamed: R14.2, U1.3 (+)
unnamed: R13.2, R17.1, U1.2 (-)
unnamed: R7.1, R8.2, R10.1, U1.5 (+)
unnamed: C2.1, R9.1, U1.6 (-)
unnamed: C3.1, R14.1, U2.1 (VO), U3.1 (VCC)
unnamed: C8.2, U3.8 (CC0)
unnamed: C7.2, U3.7 (CC1)
unnamed: C13.1, R20.1, U3.16 (LPF1-IN)
unnamed: C13.2, R21.1, U3.15 (LPF1-OUT)
unnamed: C10.2, R22.2, U3.13 (LPF2-IN)
unnamed: C10.1, R23.1, R24.2, U3.14 (LPF2-OUT)
unnamed: C12.1, U3.10 (OP1-IN)
unnamed: C12.2, U3.9 (OP1-OUT)
unnamed: C11.2, U3.11 (OP2-IN)
unnamed: C11.1, R25.2, U3.12 (OP2-OUT)
unnamed: R15.2, U3.2 (REF)
unnamed: R16.2, U3.6 (VCO)
O1: C14.2, C15.2, J1.3, J9.3, R26.2, S1.7, S2.7, S3.7, S4.7, S5.7, S6.7
O2: J2.3, S1.8, S2.8, S3.8, S4.8, S5.8, S6.8
O3: J3.3, S1.9, S2.9, S3.9, S4.9, S5.9, S6.9
O4: J4.3, S1.10, S2.10, S3.10, S4.10, S5.10, S6.10
O5: J5.3, S1.11, S2.11, S3.11, S4.11, S5.11, S6.11
O6: J6.3, S1.12, S2.12, S3.12, S4.12, S5.12, S6.12
OP: J8.T, S6.C, SW6.7 (C)
